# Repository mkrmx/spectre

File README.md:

# SPECTRE

Luz LED para la cajuela de un auto que se enciende sola al abrirla, y solo cuando está oscuro.

Un sensor Hall detecta la apertura (un imán en la carrocería se aleja del sensor) y una fotorresistencia (LDR) decide si hay poca luz. Si las dos condiciones se cumplen, un MOSFET enciende la tira LED de 12 V con un encendido y apagado suave (fade). Funciona con lógica discreta: comparador LM393, transistores bipolares y un MOSFET de nivel lógico. No lleva microcontrolador ni PWM. La versión THT rev E agrega un apagado automático unos 10 minutos después de abrir, con un temporizador CD4541.

## Diseños

Hay dos versiones de placa, cada una en su carpeta y con su propia etiqueta. La SMT sigue en rev D. La THT pasó a rev E, que agrega el apagado automático, el fade simétrico y un consumo en reposo menor; los detalles están en [`tht/README.md`](tht/README.md).

| Carpeta | Versión | Placa | Sensores | Etiqueta |
|---|---|---|---|---|
| [`smt/`](smt/) | rev D | 42 x 32 mm, SMT, ensamblada de fábrica | DRV5033 y LDR soldados en la placa | `smt-rev-d` |
| [`tht/`](tht/) | rev E | 64 x 50 mm, THT, para soldar a mano | Hall y LDR por cable (J3, J4) | `tht-rev-e` (rev D: `tht-rev-d`) |

Las dos son de 2 capas, sin barrenos de montaje y con una franja libre de 1 mm en todo el contorno para los rieles de la caja. Ambas usan conectores JST VH (B2P-VH, carcasa VHR-2N) para los 12 V y la tira LED. El historial de versiones está en [`CHANGELOG.md`](CHANGELOG.md).

```
docs/   esquemático (PDF/PNG) y logo
smt/    proyecto KiCad 7 completo, Gerbers, BOM y CPL para ensamble, vistas
tht/    proyecto KiCad 7 (esquemático y PCB), Gerbers, lista de componentes, vistas y mapa de ensamble
tools/  scripts para generar, acomodar, rutear y verificar las placas (ver tools/README.md)
```

## Cómo funciona

Esta sección describe la rev D (SMT). La THT rev E usa los mismos bloques y agrega el temporizador de apagado; ver [`tht/README.md`](tht/README.md#cómo-funciona-el-apagado).

| Bloque | Piezas | Qué hace |
|---|---|---|
| Entrada | J1, D1, C1, U1, C2 | D1 protege contra polaridad invertida. U1 (78M05 / 7805) da 5 V a la lógica; los LED usan los +12 V. |
| Apertura | U2 (DRV5033), R11, C5 | Con la cajuela cerrada el imán está frente a U2 y su salida (HALL_OUT) está en bajo. Al abrir, R11 la sube a 5 V. |
| Retardo de armado | R15, C6, D4, R16, R17, U3B, R18 | HALL_OUT carga C6 por R11 + R15. Cuando DELAY pasa de VTH (2.5 V), U3B libera ARM. Son unos 1.5 s, el tiempo que necesita la LDR para leer la luz real. D4 descarga C6 de inmediato al cerrar. |
| Oscuridad | LDR1, R8, C3, R9, U3A, R10, R13 | U3A compara el divisor de la LDR con la referencia del trimpot R9. R13 da histéresis y C3 filtra parpadeos. CMP_OUT sube cuando está oscuro. |
| Compuerta Y | Q1, Q2, R1, R2, R3 | Q1 (armado) y Q2 (oscuridad) van en serie: NODO_A solo baja si ambos conducen. |
| Latch | D2, R12 | Una vez encendida, NODO_B mantiene la base de Q2 alta. Así la luz de la propia tira no apaga la lógica de oscuridad. |
| Driver y fade | Q3, R4, R5, R6, R14, D3, R7, C4, Q4 | Q3 invierte NODO_A. El gate de Q4 carga rápido por D3 + R14 (fade de encendido) y descarga lento por R6 (fade de apagado). R7 fija el voltaje final del gate. |
| Salida | Q4, J2 | El MOSFET conmuta el negativo de la tira LED (LED_NEG). |

### Conexiones (rev D, versión SMT)

| Red | Pines |
|---|---|
| `+12V_IN` | D1.2, J1.1 |
| `+12V` | C1.1, D1.1, J2.1, U1.1 |
| `+5V` | C2.1, C5.1, R3.1, R5.1, R8.1, R9.1, R10.1, R11.1, R16.1, R18.1, U1.3, U2.1, U3.8 |
| `GND` | C1.2, C2.2, C3.2, C4.2, C5.2, C6.2, J1.2, LDR1.2, Q2.2, Q3.2, Q4.3, R7.2, R9.3, R17.2, U1.2, U2.3, U3.4 |
| `HALL_OUT` | D4.1, R11.2, R15.1, U2.2 |
| `DELAY` | C6.1, D4.2, R15.2, U3.5 |
| `VTH` | R16.2, R17.1, U3.6 |
| `ARM` | R1.1, R18.2, U3.7 |
| `LDR_DIV` | C3.1, LDR1.1, R8.2, R13.2, U3.3 |
| `REF` | R9.2, U3.2 |
| `CMP_OUT` | R2.1, R10.2, R13.1, U3.1 |
| `Net-(Q1-B)` | Q1.1, R1.2 |
| `Net-(Q2-B)` | Q2.1, R2.2, R12.2 |
| `LATCH` | D2.1, R12.1 |
| `Net-(Q1-E)` | Q1.2, Q2.3 |
| `NODO_A` | Q1.3, R3.2, R4.1 |
| `Net-(Q3-B)` | Q3.1, R4.2 |
| `NODO_B` | D2.2, D3.2, Q3.3, R5.2, R6.1 |
| `FAST` | D3.1, R14.1 |
| `GATE` | C4.1, Q4.1, R6.2, R7.1, R14.2 |
| `LED_NEG` | J2.2, Q4.2 |
En la versión THT, U2 se sustituye por J3 (1 = +5V, 2 = GND, 3 = HALL_OUT) y LDR1 por J4 (1 = LDR_DIV, 2 = GND). Q1–Q3 son TO-92 con orden E-B-C, así que su numeración de pines cambia; las redes son las mismas.

### Conectores
- **J1:** 1 = +12 V del auto (con fusible de 2 A), 2 = GND.
- **J2:** 1 = LED+ (+12 V), 2 = LED−.
- El pin 1 es el pad cuadrado.

## Lista de materiales

- **SMT:** [`smt/fab/spectre-BOM.csv`](smt/fab/spectre-BOM.csv) (con números de parte) y [`smt/fab/spectre-CPL.csv`](smt/fab/spectre-CPL.csv) para el ensamble.
- **THT:** tabla completa en [`tht/README.md`](tht/README.md#lista-de-componentes).

| Función | SMT (rev D) | THT (rev E) |
|---|---|---|
| Regulador | L78M05 (DPAK) | LP2950-5.0 (TO-92) |
| MOSFET | IRLR2905 (DPAK) | IRLZ44N (TO-220) |
| Comparador | LM393 (SOIC-8) | LM393 (DIP-8) |
| Transistores | MMBT2222A x3 (SOT-23) | PN2222A x4 y 2N3906 PNP (TO-92) |
| Temporizador | — | CD4541BE (DIP-14) |
| Diodo de entrada | M7 (SMA) | 1N4007 |
| Diodos de señal | 1N4148W x3 (SOD-123) | 1N4148 x4 |
| Hall | DRV5033FAQDBZR en placa | DRV5033 (TO-92) o A3144, por cable |
| LDR | GL5528 en placa | GL5528 por cable |
| C3 / C4 | Panasonic EEE-1CA470WR / EEE-1CA220WR | Electrolíticos radiales 5 mm |
| C6 (retardo) | 22 µF 0805 X5R | 22 µF electrolítico |
| Resistencias | 0603 1 % | 1/4 W, montaje vertical |
| Trimpot R9 | Bourns 3314J 10 kΩ | Bourns 3296W 10 kΩ |

## Decisiones de diseño

- **Lógica discreta en vez de microcontrolador.** Son dos NPN como compuerta Y, sin firmware, y cada etapa se puede medir con multímetro.
- **Fade con RC en el gate, sin PWM.** C4 22 µF con R14 68 kΩ y D3 para el encendido, y R6 100 kΩ para el apagado. R14 era de 10 kΩ hasta la versión THT rev C.
- **Histéresis y filtro en la LDR.** R13 y C3 evitan que la luz parpadee en el umbral.
- **Latch.** Sin él, la luz de la propia tira LED haría que la LDR apagara el circuito.
- **Retardo de armado (rev D).** Al abrir de día, la LDR todavía venía de la cajuela cerrada y leía "oscuro"; el Hall armaba al instante y el latch dejaba la luz encendida. El RC más U3B (la mitad libre del LM393) retrasa el armado unos 1.5 s. C6 subió de 10 µF a 22 µF tras probarlo en protoboard.
- **DRV5033 en vez de A3144.** Es omnipolar (funciona con cualquier polo del imán) y más sensible, así que basta un imán pequeño.
- **JST VH.** Conector con seguro y apto para la corriente de la tira. Además J1 y J2 usan la misma carcasa VHR-2N.
- **Montaje por rieles.** Sin barrenos y con 1 mm libre de cobre y componentes en todo el borde, para que la caja impresa en 3D sostenga la placa por los costados.
- **Placa.** 2 capas con plano de GND en ambas caras. Pistas de potencia de 1.2 mm, de señal de 0.4 mm. DRC sin errores y netlist verificada pin por pin contra el esquemático.
- **Corriente.** D1 (1 A) limita la corriente total. Para tiras de más de ~0.8 A conviene un diodo de 2–3 A.

## Ajuste
De noche, con la cajuela abierta, tapa la LDR y gira R9 hasta que encienda. Para repetir la prueba, acerca y aleja el imán y espera unos 2 s, porque el latch mantiene la luz encendida.

## Licencia
MIT, ver [`LICENSE`](LICENSE).

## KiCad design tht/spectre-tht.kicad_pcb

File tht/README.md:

# SPECTRE THT — rev E (64 x 50 mm)

Mismo concepto que la rev D (Hall + LDR, retardo de armado, latch y fade), con tres cambios:

- **Apagado automático:** un CD4541 apaga la tira unos 10 minutos después de abrir la cajuela.
- **Fade simétrico:** el encendido y el apagado tienen cada uno su propio camino RC.
- **Menor consumo en reposo:** pasa de unos 14 mA a unos 5 mA.

Esta es la primera versión THT con esquemático propio: `spectre-tht.kicad_sch`.

## Cambios contra la rev D
| Bloque | rev D | rev E | Por qué |
|---|---|---|---|
| Apagado | — | U4 CD4541, Q5, Q6, R20–R25, C7, C8, J5 | Se apaga sola aunque la cajuela se quede abierta |
| Regulador | LM7805 (TO-220) | U1 LP2950-5.0 (TO-92) + C2 10 µF | Iq de 75 µA en vez de unos 5 mA |
| Inversor | Q3 NPN + R5 1 kΩ a +5 V | Q3 PNP 2N3906 + R5 4.7 kΩ a GND | No gasta corriente con la luz apagada (antes, unos 5 mA) |
| Fade | R6 100 kΩ en paralelo con D3 + R14 | D3 + R14 68 kΩ (encendido), D5 + R6 39 kΩ (apagado) | τ de encendido ≈ 1.5 s y τ de apagado ≈ 1 s, cada uno ajustable por separado |

## Cómo funciona el apagado
1. **Cajuela cerrada:** HALL_OUT está en bajo. Q5 no conduce, R21 pone MR (pin 6) en alto y el CD4541 queda en reset, con el oscilador detenido.
2. **Al abrir:** HALL_OUT sube, Q5 baja MR y el contador arranca. Unos 1.5 s después U3B libera ARM, igual que en la rev D.
3. **Al terminar el conteo:** después de 2^15 ciclos, TOUT (pin 8) sube y se queda así (modo de ciclo único). Q6 lleva ARM a GND, Q1 se corta y la tira se apaga con su fade. Con eso también se suelta el latch.
4. **Al cerrar:** MR vuelve a alto y el contador se reinicia. La siguiente apertura da otros 10 minutos completos.

**Configuración fija de U4:**

| Pin | Señal | Nivel | Efecto |
|---|---|---|---|
| 5 | AR | 1 | Sin auto-reset |
| 10 | MODE | 0 | Ciclo único |
| 9 | Q/Q̄ | 0 | Salida baja en reset |
| 13 | B | 1 | — |
| 12 | A | 1 (por R24) | 16 etapas |

**Tiempo:** T ≈ 2^15 · 2.3 · R22 · C8 = 32768 · 2.3 · 82 kΩ · 100 nF ≈ 618 s.

A 53 Hz el oscilador queda por debajo del rango en el que la hoja de datos garantiza la fórmula (1–100 kHz). Por eso conviene medir el tiempo real (ver Ajuste).

## Placa
- **Medidas:** 64 x 50 mm, 2 capas, FR-4 1.6 mm, cobre 1 oz.
- **Contorno:** esquinas redondeadas (r = 2 mm), sin barrenos y con una franja libre de 1 mm en todo el borde.
- **Acomodo por bloques:**
  - Sensores a la izquierda (J3, J4).
  - Retardo de armado arriba.
  - Lógica al centro.
  - Temporizador abajo a la izquierda.
  - Fade abajo al centro.
  - Potencia a la derecha (J1, D1, U1, Q4, J2).
- **Pistas:**
  - +12 V, +12V_IN y LED− son de 1.2 mm.
  - Las de señal son de 0.4 mm.
  - GND va por planos en ambas caras.
  - No hay vías.
- **Verificación:**
  - DRC: 0 errores y 0 conexiones pendientes (`fab/drc.rpt`).
  - Netlist del esquemático contra PCB, pad por pad: 51 componentes, 31 redes, 0 diferencias.
- **Gerbers:** `fab/spectre-tht-gerbers.zip` incluye cobre, máscara, serigrafía, contorno, taladros (Excellon, 129 barrenos) y mapa de taladros. Es lo que se sube a la fábrica.

## Lista de componentes
| Ref | Valor | Tipo / encapsulado |
|---|---|---|
| R1, R2, R3, R4, R8, R10, R11, R12, R18, R25 | 10 kΩ (x10) | Resistencia 1/4 W, montaje vertical |
| R13, R15, R16, R17, R21, R24 | 100 kΩ (x6) | Resistencia 1/4 W, montaje vertical |
| R5 | 4.7 kΩ | Resistencia 1/4 W, montaje vertical |
| R6 | 39 kΩ | Resistencia 1/4 W, montaje vertical |
| R14 | 68 kΩ | Resistencia 1/4 W, montaje vertical |
| R7 | 1 MΩ | Resistencia 1/4 W, montaje vertical |
| R20 | 220 kΩ | Resistencia 1/4 W, montaje vertical |
| R22 | 82 kΩ | Resistencia 1/4 W 1 %, montaje vertical (Rtc) |
| R23 | 180 kΩ | Resistencia 1/4 W, montaje vertical (Rs ≈ 2·Rtc) |
| R9 | 10 kΩ | Trimpot multivuelta Bourns 3296W (vertical) |
| C1 | 0.33 µF 50 V | Cerámico, paso 2.5 mm |
| C5, C7 | 0.1 µF 50 V (x2) | Cerámico, paso 2.5 mm |
| C8 | 100 nF 63 V | Película MKS2/MKT, paso 5 mm (Ctc, no usar cerámico) |
| C2 | 10 µF 16 V | Electrolítico radial 5 mm, paso 2 mm |
| C3 | 47 µF 16 V | Electrolítico radial 5 mm, paso 2 mm |
| C4, C6 | 22 µF 16 V (x2) | Electrolítico radial 5 mm, paso 2 mm |
| D1 | 1N4007 | Rectificador DO-41, vertical |
| D2, D3, D4, D5 | 1N4148 (x4) | Diodo de señal DO-35, vertical |
| Q1, Q2, Q5, Q6 | PN2222A / 2N2222A plástico (x4) | NPN TO-92 (E-B-C) |
| Q3 | 2N3906 | PNP TO-92 (E-B-C) |
| Q4 | IRLZ44N | MOSFET N nivel lógico TO-220 |
| U1 | LP2950-5.0 (LP2950CZ-5.0 / LP2950-50LP) | LDO 5 V TO-92 (OUT-GND-IN) |
| U3 | LM393 | Comparador dual DIP-8 (zócalo opcional) |
| U4 | CD4541BE (o MC14541B) | Temporizador programable DIP-14 (zócalo opcional) |
| J1, J2 | JST B2P-VH | Header VH 2 pines vertical; carcasa VHR-2N del lado del cable |
| J3 | Header 1x3, 2.54 mm | Cable al sensor Hall |
| J4 | Header 1x2, 2.54 mm | Cable a la LDR |
| J5 | Header 1x2, 2.54 mm + jumper | Modo de prueba del temporizador |

**Fuera de la placa:** sensor Hall DRV5033 (TO-92) o A3144 con imán, LDR GL5528, conectores Dupont y fusible de 2 A en la línea de 12 V.

## Conectores
- **J1:** 1 = +12 V del auto, 2 = GND.
- **J2:** 1 = LED+ (+12 V), 2 = LED−.
- **J3 (Hall):** 1 = +5 V, 2 = GND, 3 = salida del Hall.
- **J4 (LDR):** 1 = LDR_DIV, 2 = GND.
- **J5:** sin jumper = 10 min; con jumper = modo de prueba.

El pin 1 de cada conector es el pad cuadrado.

## Orientación al soldar
- **Electrolíticos (C2, C3, C4, C6):** la pata larga (+) va al pad marcado "+".
- **Diodos (D1–D5):** la banda del cátodo va al pad cuadrado.
- **Transistores TO-92 (Q1–Q3, Q5, Q6) y U1:**
  - El pad cuadrado es el pin 1: emisor en los transistores, OUT en U1.
  - La cara plana va según el dibujo de la serigrafía.
  - Ojo: Q3 es PNP.
- **Q4:** la pestaña metálica va hacia la franja angosta del rectángulo de serigrafía. G-D-S.
- **U3 y U4:** el pin 1 es el pad cuadrado, del lado de la muesca.

## Ajuste
- **R9:** se ajusta igual que en la rev D. De noche, con la cajuela abierta, tapa la LDR y gira hasta que encienda.
- **Tiempo de apagado:**
  1. Pon el jumper en J5 (A = 0, 2^9 ciclos) y abre la cajuela de noche.
  2. Mide cuánto tarda en apagarse; debería ser unos 10 s.
  3. Multiplica ese tiempo por 64 para obtener el tiempo real.
  4. Quita el jumper.
  5. Si quieres otro tiempo, cambia R22. El tiempo es proporcional a R22.
- **Puntos de medición:**
  - U4 pin 6 (MR): 5 V con la cajuela cerrada y 0 V abierta.
  - U4 pin 8 (TOUT): pasa a 5 V al cumplirse el tiempo.
  - U3 pin 7 (ARM): baja a 0 V en ese momento.

## Consumo en reposo (cajuela cerrada)
| Pieza | Consumo |
|---|---|
| Hall | ≈ 2.7 mA |
| R11, R18 y R9 | ≈ 0.5 mA cada una |
| LM393 | ≈ 0.4 mA |
| LP2950 | 75 µA |
| CD4541 en reset | µA |
| **Total** | **≈ 4.5–5 mA** (rev D: ≈ 14 mA) |

## Archivos
| Archivo | Contenido |
|---|---|
| `spectre-tht.kicad_pro` | Proyecto KiCad 7 |
| `spectre-tht.kicad_sch` | Esquemático |
| `spectre-tht.kicad_pcb` | PCB |
| `spectre-tht-esquematico.pdf` | Esquemático en PDF |
| `img/esquematico.png` | Esquemático en PNG |
| `img/vista-superior.png` | Vista de la cara de componentes |
| `img/vista-inferior.png` | Vista de la cara inferior |
| `img/mapa-ensamble.png` | Mapa de ensamble; en rojo lo nuevo y en ámbar lo que cambió |
| `fab/spectre-tht-gerbers.zip` | Gerbers y taladros para la fábrica |
| `fab/drc.rpt` | Reporte del DRC |

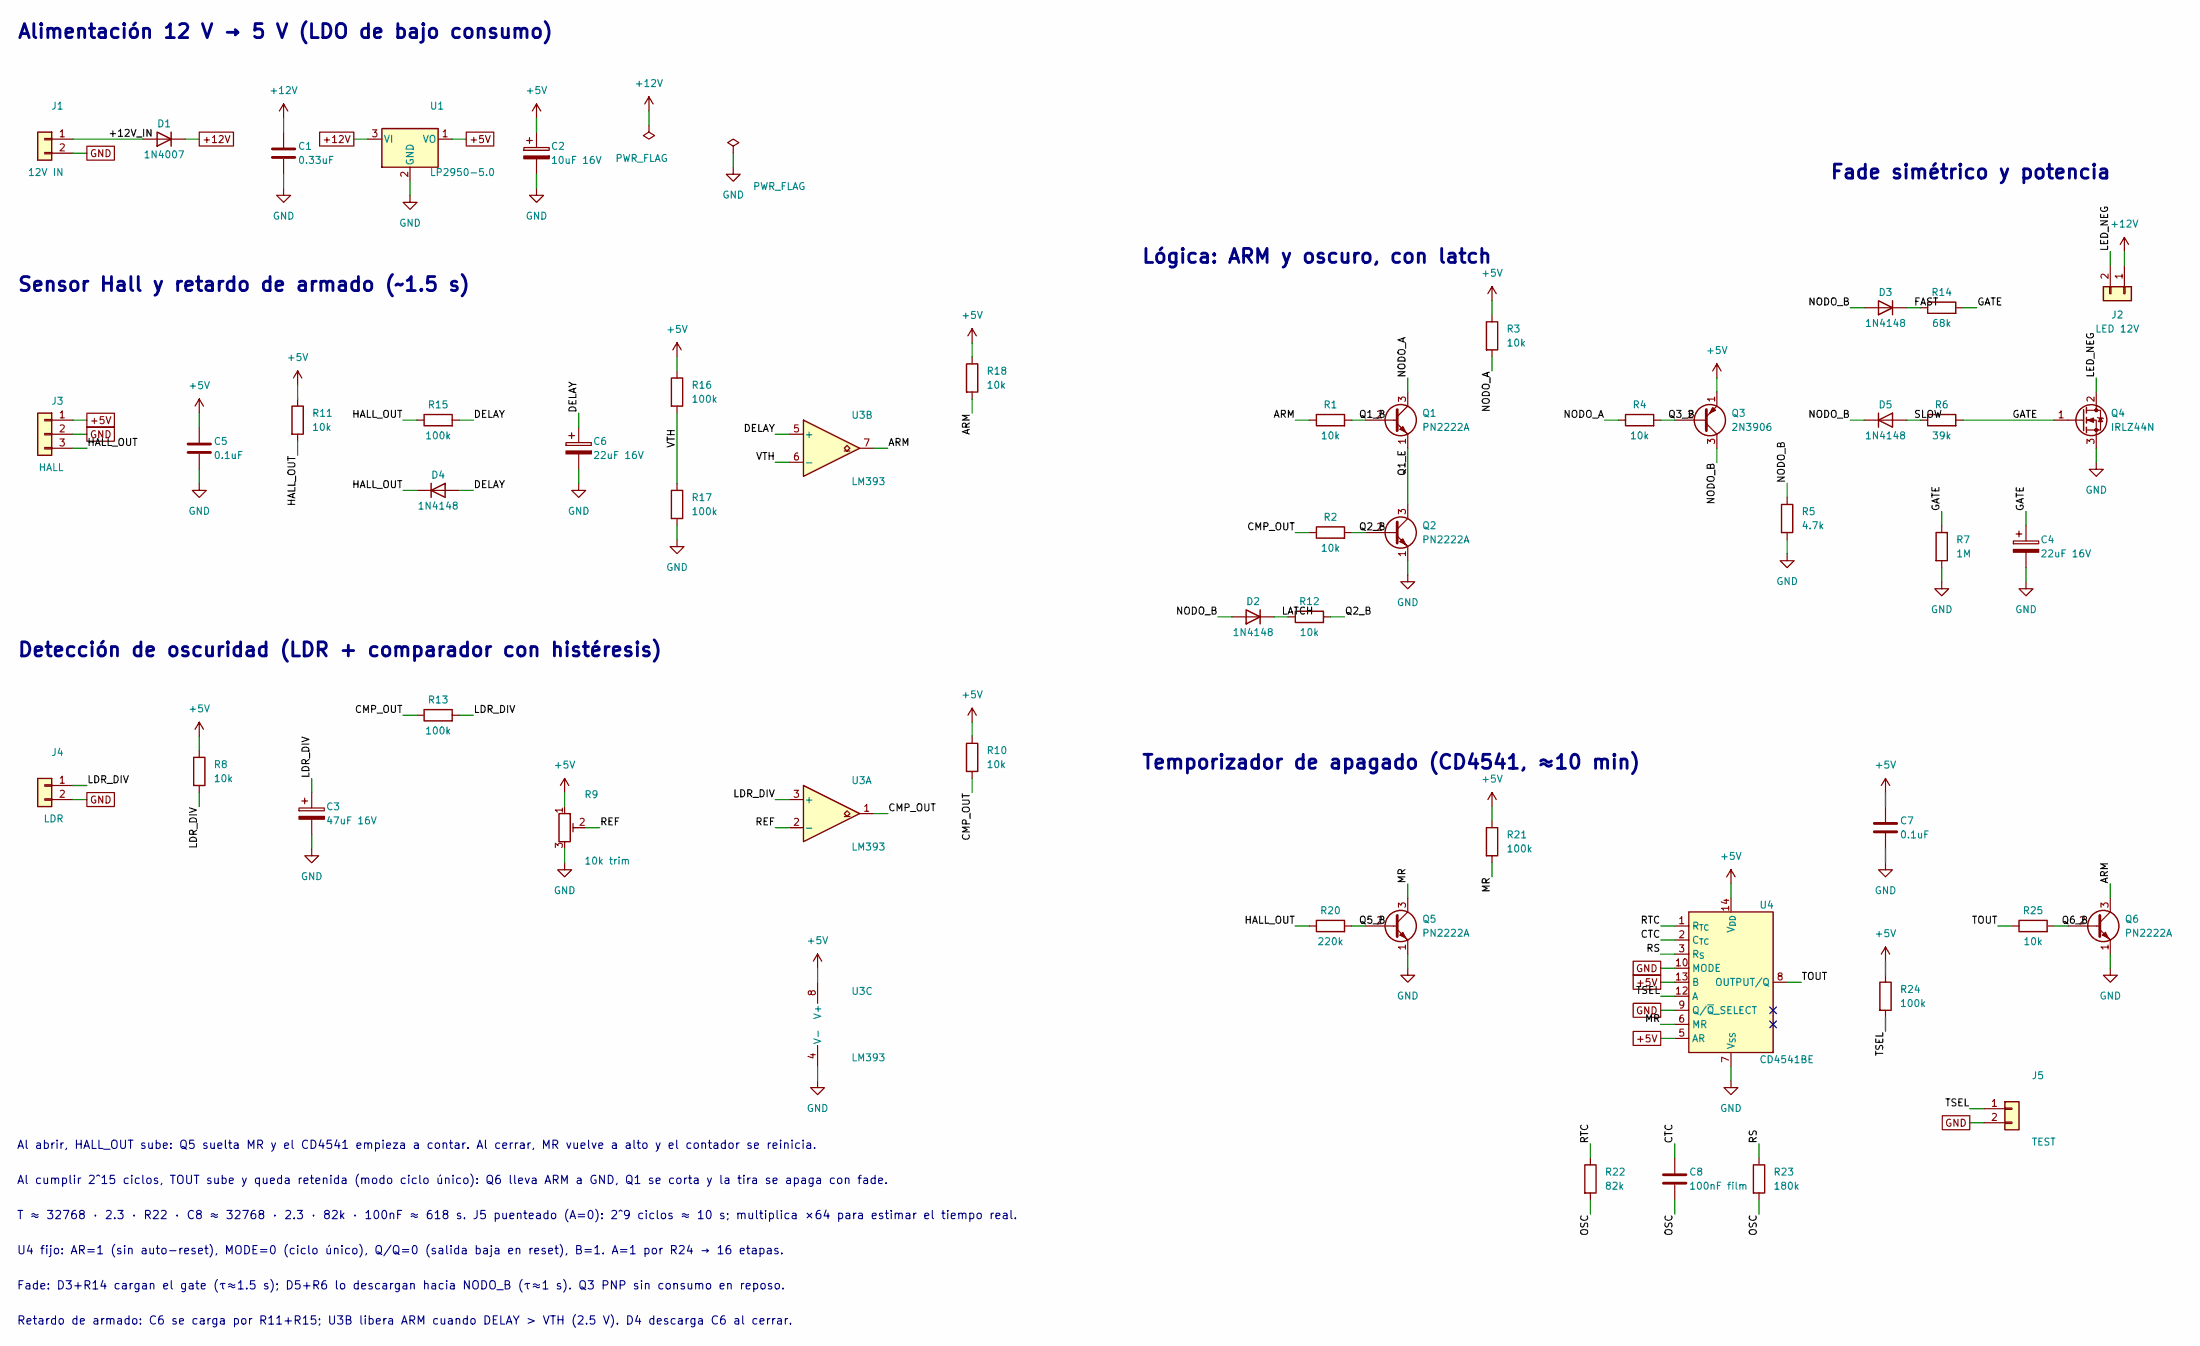
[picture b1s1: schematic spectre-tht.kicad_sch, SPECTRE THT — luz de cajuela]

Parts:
C1: 0.33uF; C_Disc_D3.8mm_W2.6mm_P2.50mm
C2: 10uF 16V; CP_Radial_D5.0mm_P2.00mm
C3: 47uF 16V; CP_Radial_D5.0mm_P2.00mm
C4, C6: 22uF 16V; CP_Radial_D5.0mm_P2.00mm
C5, C7: 0.1uF; C_Disc_D3.8mm_W2.6mm_P2.50mm
C8: 100nF film; C_Rect_L7.2mm_W2.5mm_P5.00mm_FKS2_FKP2_MKS2_MKP2
D1: 1N4007; D_DO-41_SOD81_P5.08mm_Vertical_KathodeUp
D2, D3, D4, D5: 1N4148; D_DO-35_SOD27_P2.54mm_Vertical_KathodeUp
J1: 12V IN; JST_VH_B2P-VH_1x02_P3.96mm_Vertical
J2: LED 12V; JST_VH_B2P-VH_1x02_P3.96mm_Vertical
J3: HALL; PinHeader_1x03_P2.54mm_Vertical
J4: LDR; PinHeader_1x02_P2.54mm_Vertical
J5: TEST; PinHeader_1x02_P2.54mm_Vertical
Q1, Q2, Q5, Q6: PN2222A; TO-92_Inline_Wide
Q3: 2N3906; TO-92_Inline_Wide
Q4: IRLZ44N; TO-220-3_Vertical
R1, R2, R3, R4, R8, R10, R11, R12, R18, R25: 10k; R_Axial_DIN0207_L6.3mm_D2.5mm_P2.54mm_Vertical
R5: 4.7k; R_Axial_DIN0207_L6.3mm_D2.5mm_P2.54mm_Vertical
R6: 39k; R_Axial_DIN0207_L6.3mm_D2.5mm_P2.54mm_Vertical
R7: 1M; R_Axial_DIN0207_L6.3mm_D2.5mm_P2.54mm_Vertical
R9: 10k trim; Potentiometer_Bourns_3296W_Vertical
R13, R15, R16, R17, R21, R24: 100k; R_Axial_DIN0207_L6.3mm_D2.5mm_P2.54mm_Vertical
R14: 68k; R_Axial_DIN0207_L6.3mm_D2.5mm_P2.54mm_Vertical
R20: 220k; R_Axial_DIN0207_L6.3mm_D2.5mm_P2.54mm_Vertical
R22: 82k; R_Axial_DIN0207_L6.3mm_D2.5mm_P2.54mm_Vertical
R23: 180k; R_Axial_DIN0207_L6.3mm_D2.5mm_P2.54mm_Vertical
U1: LP2950-5.0; TO-92_Inline_Wide
U3: LM393; DIP-8_W7.62mm
U4: CD4541BE; DIP-14_W7.62mm

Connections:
+5V: C2.1, C5.1, C7.1, J3.1, Q3.1 (E), R3.1, R8.1, R9.1, R10.1, R11.1, R16.1, R18.1, R21.1, R24.1, U1.1 (VO), U3.8 (V+), U4.5 (AR), U4.13 (B), U4.14 (V_{DD})
+12V: C1.1, D1.1 (K), J2.1, U1.3 (VI)
/+12V_IN: D1.2 (A), J1.1
/ARM: Q6.3 (C), R1.1, R18.2, U3.7
/CMP_OUT: R2.1, R10.2, R13.1, U3.1
/CTC: C8.1, U4.2 (C_{TC})
/DELAY: C6.1, D4.2 (A), R15.2, U3.5 (+)
/FAST: D3.1 (K), R14.1
/GATE: C4.1, Q4.1 (G), R6.2, R7.1, R14.2
/HALL_OUT: D4.1 (K), J3.3, R11.2, R15.1, R20.1
/LATCH: D2.1 (K), R12.1
/LDR_DIV: C3.1, J4.1, R8.2, R13.2, U3.3 (+)
/LED_NEG: J2.2, Q4.2 (D)
/MR: Q5.3 (C), R21.2, U4.6 (MR)
/NODO_A: Q1.3 (C), R3.2, R4.1
/NODO_B: D2.2 (A), D3.2 (A), D5.1 (K), Q3.3 (C), R5.1
/OSC: C8.2, R22.2, R23.2
/Q1_B: Q1.2 (B), R1.2
/Q1_E: Q1.1 (E), Q2.3 (C)
/Q2_B: Q2.2 (B), R2.2, R12.2
/Q3_B: Q3.2 (B), R4.2
/Q5_B: Q5.2 (B), R20.2
/Q6_B: Q6.2 (B), R25.2
/REF: R9.2, U3.2 (-)
/RS: R23.1, U4.3 (R_{S})
/RTC: R22.1, U4.1 (R_{TC})
/SLOW: D5.2 (A), R6.1
/TOUT: R25.1, U4.8 (OUTPUT/Q)
/TSEL: J5.1, R24.2, U4.12 (A)
/VTH: R16.2, R17.1, U3.6 (-)
GND: C1.2, C2.2, C3.2, C4.2, C5.2, C6.2, C7.2, J1.2, J3.2, J4.2, J5.2, Q2.1 (E), Q4.3 (S), Q5.1 (E), Q6.1 (E), R5.2, R7.2, R9.3, R17.2, U1.2 (GND), U3.4 (V-), U4.7 (V_{SS}), U4.9 (Q/~Q_SELECT), U4.10 (MODE)

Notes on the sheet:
Alimentación 12 V → 5 V (LDO de bajo consumo)
Sensor Hall y retardo de armado (~1.5 s)
Detección de oscuridad (LDR + comparador con histéresis)
Lógica: ARM y oscuro, con latch
Fade simétrico y potencia
Temporizador de apagado (CD4541, ≈10 min)
Al abrir, HALL_OUT sube: Q5 suelta MR y el CD4541 empieza a contar. Al cerrar, MR vuelve a alto y el contador se reinicia.
Al cumplir 2^15 ciclos, TOUT sube y queda retenida (modo ciclo único): Q6 lleva ARM a GND, Q1 se corta y la tira se apaga con fade.
T ≈ 32768 · 2.3 · R22 · C8 ≈ 32768 · 2.3 · 82k · 100nF ≈ 618 s. J5 puenteado (A=0): 2^9 ciclos ≈ 10 s; multiplica ×64 para estimar el tiempo real.
U4 fijo: AR=1 (sin auto-reset), MODE=0 (ciclo único), Q/Q=0 (salida baja en reset), B=1. A=1 por R24 → 16 etapas.
Fade: D3+R14 cargan el gate (τ≈1.5 s); D5+R6 lo descargan hacia NODO_B (τ≈1 s). Q3 PNP sin consumo en reposo.
Retardo de armado: C6 se carga por R11+R15; U3B libera ARM cuando DELAY > VTH (2.5 V). D4 descarga C6 al cerrar.

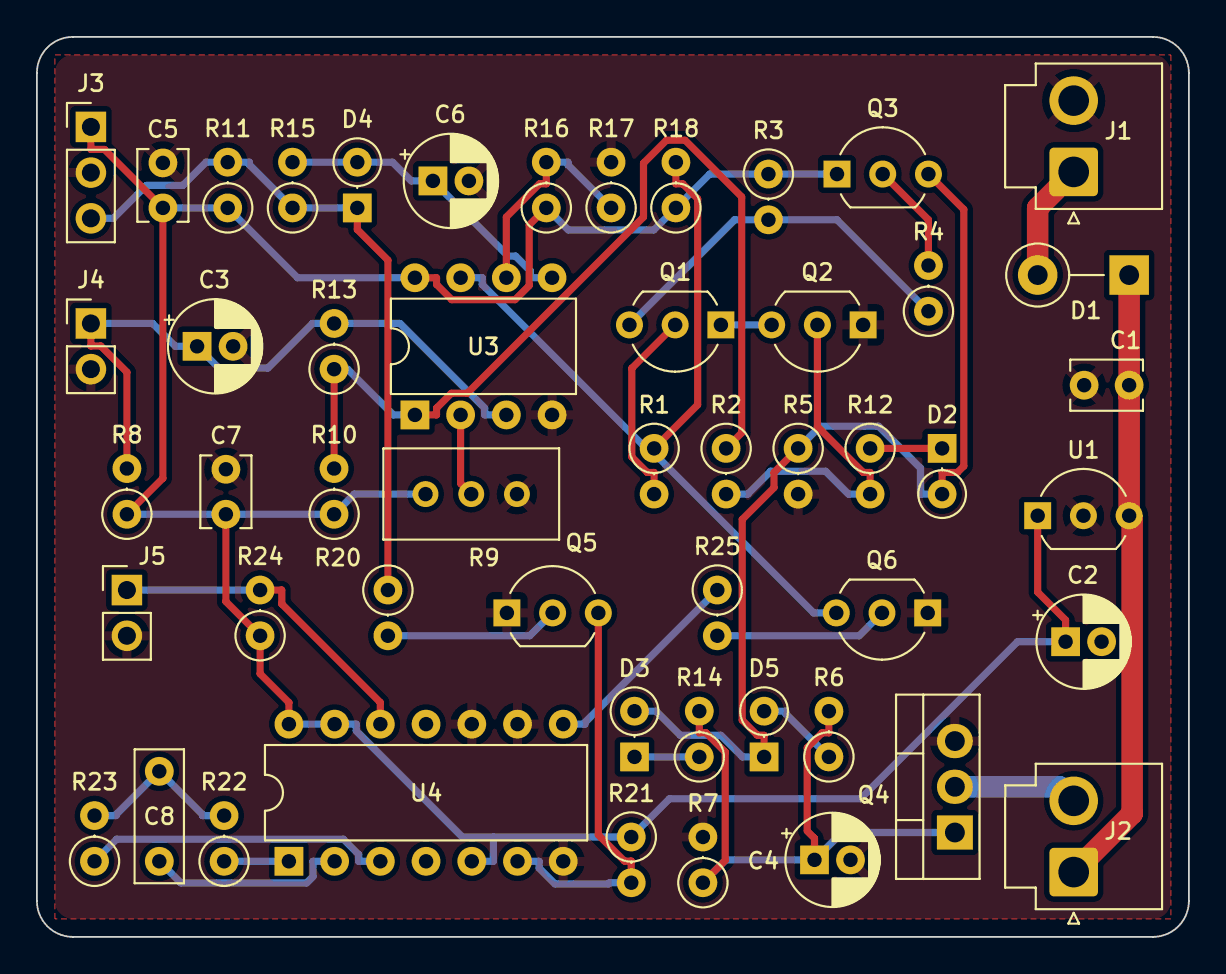
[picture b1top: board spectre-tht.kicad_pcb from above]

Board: 2 copper layers, 64.0 x 50.0 mm, 51 parts (0 on the bottom side), 31 nets.

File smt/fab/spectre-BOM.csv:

Comment,Designator,Footprint,Manufacturer Part,Descripción,Cantidad,Montaje
0.33uF 50V X7R,C1,C_0805_2012Metric,CL21B334KBFNNNE (o equivalente),Cerámico 0805 X7R 50 V,1,SMT
0.1uF 50V X7R,C2,C_0805_2012Metric,CL21B104KBCNNNC (o equivalente),Cerámico 0805 X7R 50 V,1,SMT
47uF 16V,C3,CP_Elec_5x5.3,Panasonic EEE-1CA470WR,Electrolítico SMD,1,SMT
22uF 16V,C4,CP_Elec_4x5.4,Panasonic EEE-1CA220WR,Electrolítico SMD,1,SMT
0.1uF 50V X7R,C5,C_0603_1608Metric,CL10B104KB8NNNC (o equivalente),"Cerámico 0603 X7R 50 V, desacoplo de U2",1,SMT
22uF 16V X5R,C6,C_0805_2012Metric,"22 µF 0805 X5R, 16 V o más (o equivalente)","Cerámico 0805 X5R, retardo de armado (C6)",1,SMT
M7,D1,D_SMA,"M7 (1000 V 1 A, SMA)",Diodo rectificador,1,SMT
1N4148W,"D2,D3,D4",D_SOD-123,1N4148W (SOD-123),Diodo de señal,3,SMT
MMBT2222A,"Q1,Q2,Q3",SOT-23,MMBT2222A (SOT-23),NPN,3,SMT
IRLR2905 DPAK,Q4,TO-252-2,IRLR2905TRPBF,"N-MOSFET nivel lógico 55 V, DPAK",1,SMT
10k,"R1,R2,R3,R4,R8,R10,R11,R12,R18",R_0603_1608Metric,0603WAF1002T5E (o equivalente),Resistencia 0603 1% 1/10 W,9,SMT
1k,R5,R_0603_1608Metric,0603WAF1001T5E (o equivalente),Resistencia 0603 1% 1/10 W,1,SMT
100k,"R6,R13,R15,R16,R17",R_0603_1608Metric,0603WAF1003T5E (o equivalente),Resistencia 0603 1% 1/10 W,5,SMT
1M,R7,R_0603_1608Metric,0603WAF1004T5E (o equivalente),Resistencia 0603 1% 1/10 W,1,SMT
10k trim 3314J,R9,Potentiometer_Bourns_3314J_Vertical,Bourns 3314J-1-103E,Trimpot 10 kΩ SMD,1,SMT
68k,R14,R_0603_1608Metric,0603WAF6802T5E (o equivalente),Resistencia 0603 1% 1/10 W,1,SMT
L78M05 DPAK,U1,TO-252-2,L78M05ABDT-TR,"Regulador 5 V 500 mA, DPAK",1,SMT
DRV5033FA,U2,SOT-23-3,DRV5033FAQDBZR,"Sensor Hall omnipolar, 3.5 mT, SOT-23 (TI)",1,SMT
LM393 SOIC-8,U3,SOIC-8_3.9x4.9mm_P1.27mm,LM393DR,Comparador dual SOIC-8,1,SMT
B2P-VH,"J1,J2",JST_VH_B2P-VH_1x02_P3.96mm_Vertical,JST B2P-VH(LF)(SN),"Header VH 2P top entry, THT; acopla con VHR-2N",2,THT
GL5528,LDR1,R_LDR_5.1x4.3mm_P3.4mm_Vertical,GL5528,"Fotorresistencia 5 mm, THT",1,THT

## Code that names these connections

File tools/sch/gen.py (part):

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place("R11", "R", 34, 69, value="10k", fp=FP["R"], refpos=(1.8, -0.7, "left"), valpos=(1.8, 0.8, "left"))
pwr("+5V", 34, 64); W((34, 64), ("R11", "1"))
W(("U2", "2"), (41, 75)); W(("R11", "2"), (34, 75))
label("HALL_OUT", 31, 75)
place("R15", "R", 44, 75, r=90, value="100k", fp=FP["R"], refpos=(0, -2.6, None), valpos=(0, 2, None))
place("D4", "D", 44, 81, value="1N4148W", fp=FP["SOD"], refpos=(0, -2.2, None), valpos=(0, 2.4, None))
W((38, 75), (38, 81), ("D4", "1"))
W(("R15", "2"), (74, 75))
W(("D4", "2"), (52, 81), (52, 75))
label("DELAY", 60, 75)
place("C6", "C", 56, 80, value="10uF", fp=FP["C0805"], refpos=(1.8, -0.7, "left"), valpos=(1.8, 0.8, "left"))
W((56, 75), ("C6", "1")); pwr("GND", 56, 85); W(("C6", "2"), (56, 85))
place("U3", "CMP", 80, 77, unit=2, value="LM393", fp=FP["SOIC"], refpos=(0, -5.5, None), valpos=(0, 4.5, None))
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W(("R16", "2"), ("R17", "1"))
pwr("GND", 68, 95)
W((68, 89), (72, 89), (72, 79), ("U3", "6"))
label("VTH", 69, 89)
place("R18", "R", 90, 71, value="10k", fp=FP["R"], refpos=(1.8, -0.7, "left"), valpos=(1.8, 0.8, "left"))
pwr("+5V", 90, 66); W((90, 66), ("R18", "1"))
W(("R18", "2"), (90, 77))
W(("U3", "7"), (103, 77))
label("ARM", 92, 77)

# ======================= C) LDR + COMPARADOR =======================
text("Detección de oscuridad (LDR + comparador con histéresis)", 14, 104)
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pwr("GND", 50, 132); W(("C3", "2"), (50, 132))
place("U3", "CMP", 80, 126, unit=1, value="LM393", fp=FP["SOIC"], refpos=(0, -5.5, None), valpos=(0, 4.5, None))
W((40, 124), (50, 124), (60, 124), ("U3", "3"))
label("LDR_DIV", 41, 124)
place("R13", "R", 73, 117, r=270, value="100k", fp=FP["R"], refpos=(0, -2, None), valpos=(0, 2, None))
W((60, 124), (60, 117), ("R13", "2"))
W(("R13", "1"), (92, 117), (92, 126))
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pwr("+5V", 96, 115); W((96, 115), ("R10", "1"))
W(("R10", "2"), (96, 126))
W(("U3", "1"), (100, 126), (100, 89), (103, 89))
label("CMP_OUT", 87, 126)
place("U3", "CMP", 82, 148, unit=3, value="LM393", fp=FP["SOIC"], refpos=(3, -1, "left"), valpos=(3, 1, "left"))
pwr("+5V", 80, 140); W((80, 140), ("U3", "8"))
pwr("GND", 80, 156); W(("U3", "4"), (80, 156))
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W((110, 89), (110, 102), ("R12", "2"))
place("D2", "D", 122, 102, value="1N4148W", fp=FP["SOD"], refpos=(0, -2.2, None), valpos=(0, 2.4, None))
W(("R12", "1"), ("D2", "1"))
label("LATCH", 117, 102)
W((118, 71), (125, 71))
label("NODO_A", 119, 71)
place("R4", "R", 128, 71, r=90, value="10k", fp=FP["R"], refpos=(0, -2, None), valpos=(0, 2, None))
place("Q3", "NPN", 138, 71, value="MMBT2222A", fp=FP["SOT"], refpos=(0.5, -6.6, "right"), valpos=(0.5, -5.1, "right"))
W(("R4", "2"), ("Q3", "1"))
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pwr("+5V", 140, 54); W((140, 54), ("R5", "1"))
W(("R5", "2"), ("Q3", "3"))
W((140, 65), (157, 65))
label("NODO_B", 141, 65)
W((146, 65), (146, 102), ("D2", "2"))

# ======================= E) FADE + POTENCIA =======================
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W((150, 65), (150, 72), ("D3", "2"))
place("R14", "R", 161, 72, r=90, value="68k", fp=FP["R"], refpos=(0, 2, None), valpos=(0, 3.6, None))
W(("D3", "1"), ("R14", "1"))
label("FAST", 157, 72)
W(("R14", "2"), (168, 72), (168, 65))
place("R7", "R", 172, 72, value="1M", fp=FP["R"], refpos=(1.8, -0.7, "left"), valpos=(1.8, 0.8, "left"))
W((172, 65), ("R7", "1")); pwr("GND", 172, 78); W(("R7", "2"), (172, 78))
place("C4", "CP", 179, 72, value="22uF 16V", fp=FP["CP4"], refpos=(1.8, -0.7, "left"), valpos=(1.8, 0.8, "left"))
W((179, 65), ("C4", "1")); pwr("GND", 179, 78); W(("C4", "2"), (179, 78))
label("GATE", 164, 65)
place("Q4", "NMOS", 190, 65, value="IRLR2905", fp=FP["DPAK"], refpos=(3.5, -0.7, "left"), valpos=(3.5, 0.8, "left"))
pwr("GND", 192, 72); W(("Q4", "3"), (192, 72))
place("J2", "CONN", 210, 56, value="LED 12V", fp=FP["VH"], refpos=(0, -2.5, None), valpos=(0, 4.5, None))
W(("Q4", "2"), (192, 58), ("J2", "2"))
label("LED_NEG", 194, 58)
W(("J2", "1"), (200, 56), (200, 52))
pwr("+12V", 200, 52)

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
